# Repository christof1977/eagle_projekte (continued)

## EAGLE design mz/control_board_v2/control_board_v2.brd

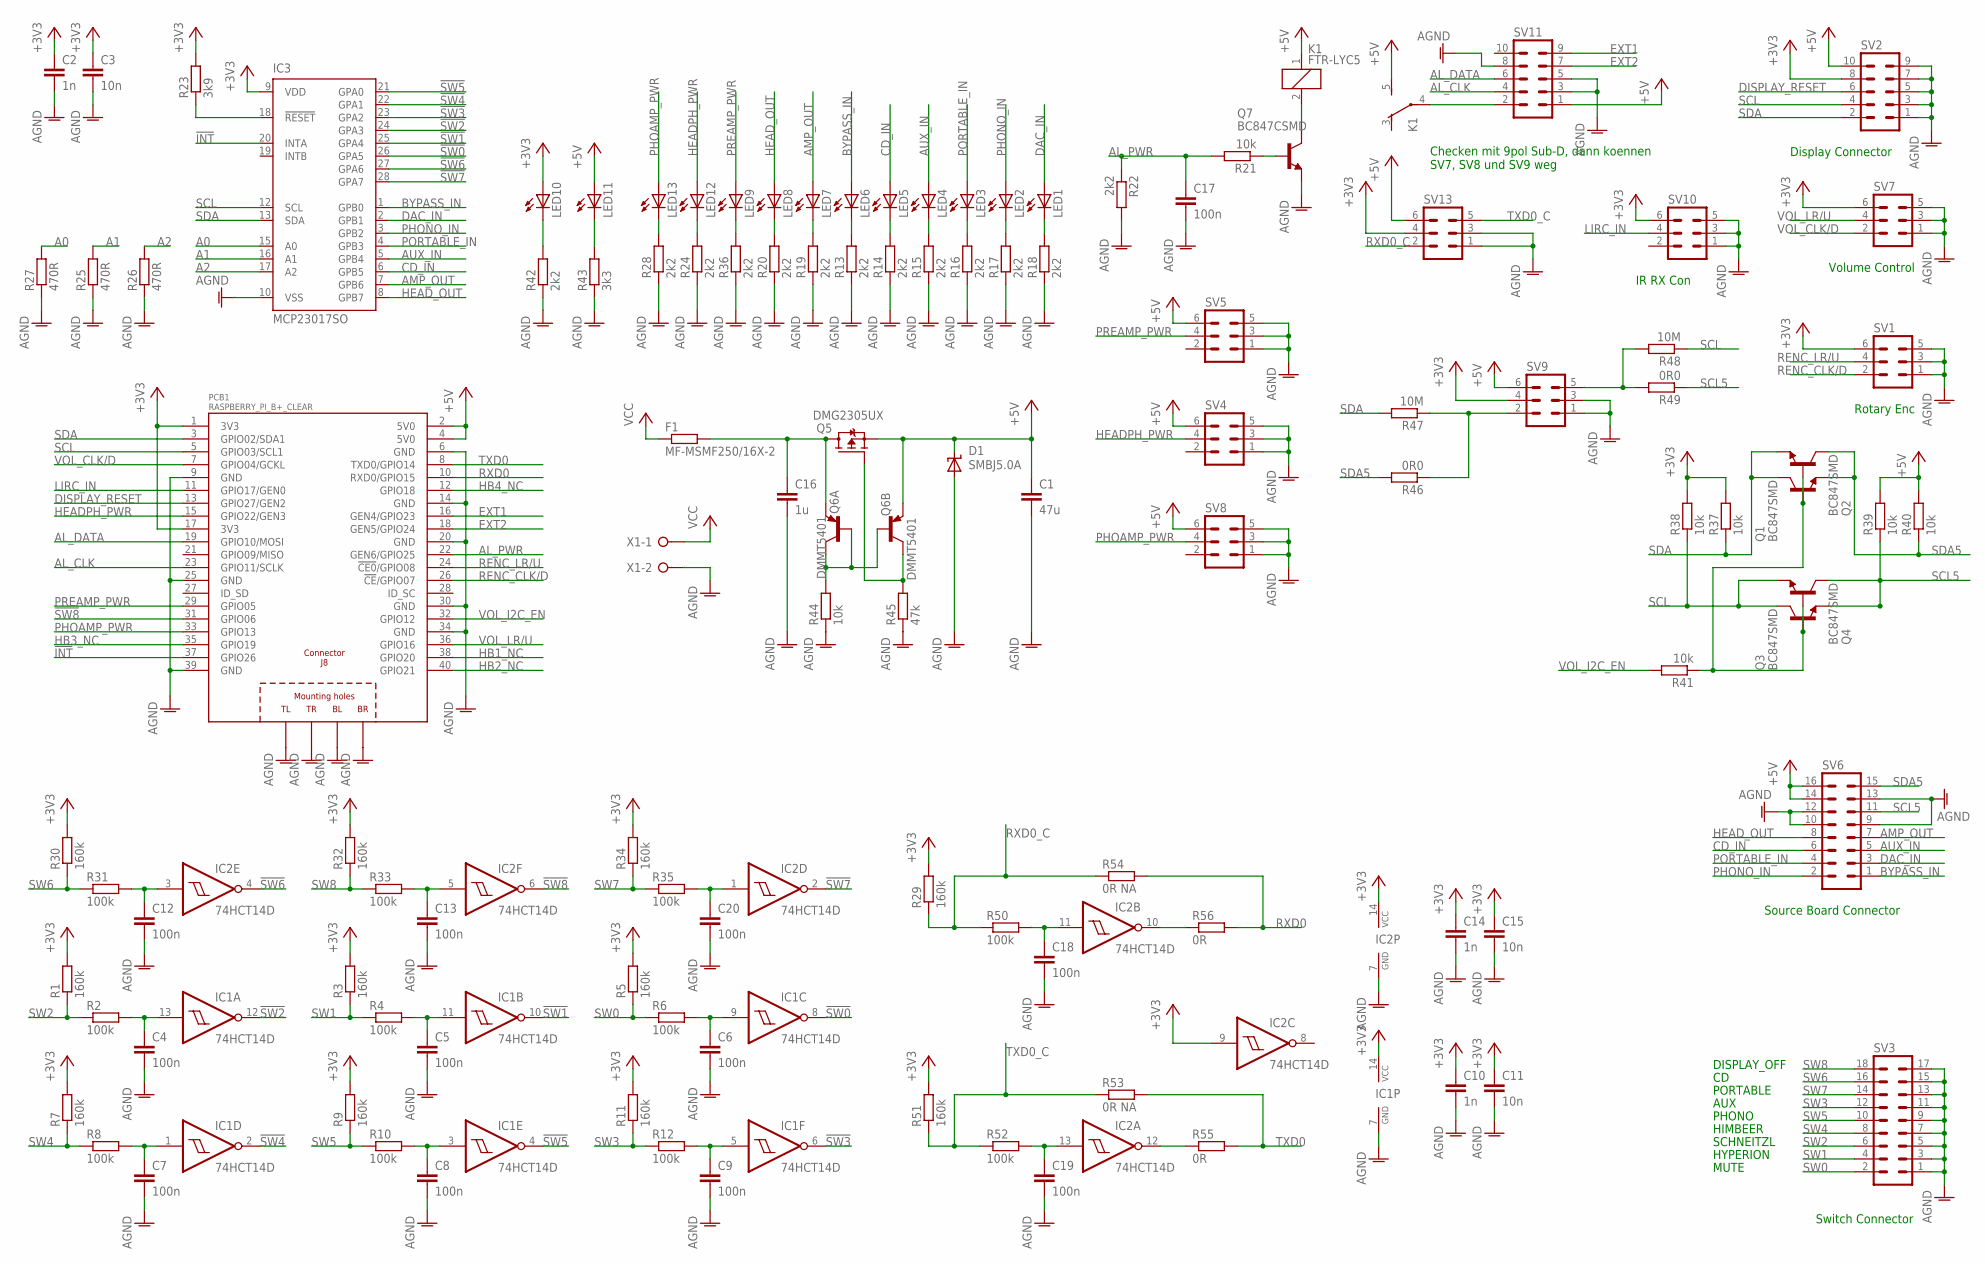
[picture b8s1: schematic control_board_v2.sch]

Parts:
C1: 47u; C1812
C2, C10, C14: 1n; C0603
C3, C11, C15: 10n; C0603
C4, C5, C6, C7, C8, C9, C12, C13, C17, C18, C19, C20: 100n; C0603
C16: 1u; C1206
D1: SMBJ5.0A; SMBJ
F1: MF-MSMF250/16X-2; 1812X7R
IC1, IC2: 74HCT14D; SO14
IC3: MCP23017SO; SO28W
K1: FTR-LYC5; FTR-LYC
LED1, LED2, LED3, LED4, LED5, LED6, LED7, LED8, LED9, LED10, LED11, LED12, LED13: LEDCHIPLED_0603; CHIPLED_0603
PCB1: RASPBERRY_PI_B+_CLEAR; RASPBERRY_PI_PLUS_CLEAR
Q1, Q2, Q3, Q4: BC847SMD; SOT23
Q5: DMG2305UX; SOT23
Q6: DMMT5401; SOT23-6
Q7: BC847CSMD; SOT23
R1, R3, R5, R7, R9, R11, R29, R30, R32, R34, R51: 160k; R0603
R2, R4, R6, R8, R10, R12, R31, R33, R35, R50, R52: 100k; R0603
R13, R14, R15, R16, R17, R18, R19, R20, R22, R24, R28, R36, R42: 2k2; R0603
R21, R38, R39, R40, R44: 10k; R0603
R23: 3k9; R1206
R25, R26, R27: 470R; R0603
R37, R41: 10k; R1206
R43: 3k3; R0603
R45: 47k; R0603
R46, R49: 0R0; R0603
R47, R48: 10M; R0603
R53, R54: 0R NA; R0603
R55, R56: 0R; R0603
SV1, SV4, SV5, SV7, SV8, SV9, SV10, SV13: MA03-2B; MA03-2_BORDER
SV2, SV11: MA05-2B; MA05-2_BORDER
SV3: MA09-2B; MA09-2_BORDER
SV6: MA08-2B; MA08-2_BORDER
X1: W237-02P; W237-132

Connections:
!INT: IC3.20 (INTA), PCB1.37 (GPIO26)
!SW0: IC1.8 (O), IC3.26 (GPA5)
!SW1: IC1.10 (O), IC3.25 (GPA4)
!SW2: IC1.12 (O), IC3.24 (GPA3)
!SW3: IC1.6 (O), IC3.23 (GPA2)
!SW4: IC1.2 (O), IC3.22 (GPA1)
!SW5: IC1.4 (O), IC3.21 (GPA0)
!SW6: IC2.4 (O), IC3.27 (GPA6)
!SW7: IC2.2 (O), IC3.28 (GPA7)
!SW8: IC2.6 (O), PCB1.31 (GPIO06)
+3V3: C2.1, C3.1, C10.1, C11.1, C14.1, C15.1, IC1.14 (VCC), IC2.9 (I), IC2.14 (VCC), IC3.9 (VDD), LED10.A, PCB1.1 (3V3), PCB1.17 (3V3), R1.2, R3.2, R5.2, R7.2, R9.2, R11.2, R23.2, R29.2, R30.2, R32.2, R34.2, R37.2, R38.2, R51.2, SV1.6, SV2.8, SV7.6, SV9.4, SV10.6, SV13.4
+5V: C1.1, D1.C, K1.1, K1.5 (S), LED11.A, PCB1.2 (5V0), PCB1.4 (5V0), Q5.2 (S), Q6.5 (E), R39.2, R40.2, SV2.10, SV4.6, SV5.6, SV6.14, SV6.16, SV8.6, SV9.6, SV11.1, SV13.6
A0: IC3.15 (A0), R27.2
A1: IC3.16 (A1), R25.2
A2: IC3.17 (A2), R26.2
AGND: C1.2, C2.2, C3.2, C4.2, C5.2, C6.2, C7.2, C8.2, C9.2, C10.2, C11.2, C12.2, C13.2, C14.2, C15.2, C16.2, C17.2, C18.2, C19.2, C20.2, D1.A, IC1.7 (GND), IC2.7 (GND), IC3.10 (VSS), PCB1.6 (GND), PCB1.9 (GND), PCB1.14 (GND), PCB1.20 (GND), PCB1.25 (GND), PCB1.30 (GND), PCB1.34 (GND), PCB1.39 (GND), PCB1.PE_BL (BL), PCB1.PE_BR (BR), PCB1.PE_TL (TL), PCB1.PE_TR (TR), Q7.2 (E), R13.1, R14.1, R15.1, R16.1, R17.1, R18.1, R19.1, R20.1, R22.2, R24.1, R25.1, R26.1, R27.1, R28.1, R36.1, R42.1, R43.1, R44.1, R45.1, SV1.1, SV1.3, SV1.5, SV2.1, SV2.3, SV2.5, SV2.7, SV2.9, SV3.1, SV3.3, SV3.5, SV3.7, SV3.9, SV3.11, SV3.13, SV3.15, SV3.17, SV4.1, SV4.3, SV4.5, SV5.1, SV5.3, SV5.5, SV6.9, SV6.10, SV6.12, SV6.13, SV7.1, SV7.3, SV7.5, SV8.1, SV8.3, SV8.5, SV9.1, SV9.3, SV10.1, SV10.3, SV10.5, SV11.3, SV11.5, SV11.8, SV13.1, SV13.3, X1.2
AL_CLK: PCB1.23 (GPIO11/SCLK), SV11.4
AL_DATA: PCB1.19 (GPIO10/MOSI), SV11.6
AL_PWR: C17.1, PCB1.22 (GEN6/GPIO25), R21.2, R22.1
AMP_OUT: IC3.7 (GPB6), LED7.A, SV6.7
AUX_IN: IC3.5 (GPB4), LED4.A, SV6.5
BYPASS_IN: IC3.1 (GPB0), LED6.A, SV6.1
CD_IN: IC3.6 (GPB5), LED5.A, SV6.6
DAC_IN: IC3.2 (GPB1), LED1.A, SV6.3
DISPLAY_RESET: PCB1.13 (GPIO27/GEN2), SV2.6
EXT1: PCB1.16 (GEN4/GPIO23), SV11.9
EXT2: PCB1.18 (GEN5/GPIO24), SV11.7
HB1_NC: PCB1.38 (GPIO20)
HB2_NC: PCB1.40 (GPIO21)
HB3_NC: PCB1.35 (GPIO19)
HB4_NC: PCB1.12 (GPIO18)
HEADPH_PWR: LED12.A, PCB1.15 (GPIO22/GEN3), SV4.4
HEAD_OUT: IC3.8 (GPB7), LED8.A, SV6.8
LIRC_IN: PCB1.11 (GPIO17/GEN0), SV10.4
unnamed: C20.1, IC2.1 (I), R35.2
unnamed: LED13.C, R28.2
unnamed: LED12.C, R24.2
unnamed: LED9.C, R36.2
unnamed: LED8.C, R20.2
unnamed: LED7.C, R19.2
unnamed: LED6.C, R13.2
unnamed: LED3.C, R16.2
unnamed: LED4.C, R15.2
unnamed: LED5.C, R14.2
unnamed: C12.1, IC2.3 (I), R31.2
unnamed: C4.1, IC1.13 (I), R2.2
unnamed: C13.1, IC2.5 (I), R33.2
unnamed: C5.1, IC1.11 (I), R4.2
unnamed: IC3.18 (!RESET), R23.1
unnamed: C6.1, IC1.9 (I), R6.2
unnamed: Q1.1 (B), Q2.1 (B), Q3.1 (B), Q4.1 (B), R41.1
unnamed: C7.1, IC1.1 (I), R8.2
unnamed: Q6.1 (C), Q6.2 (B), Q6.3 (B), R44.2
unnamed: C8.1, IC1.3 (I), R10.2
unnamed: K1.4, SV11.2
unnamed: LED11.C, R43.2
unnamed: C9.1, IC1.5 (I), R12.2
unnamed: LED10.C, R42.2
unnamed: Q5.1 (G), Q6.4 (C), R45.2
unnamed: C16.1, F1.2, Q5.3 (D), Q6.6 (E)
unnamed: Q7.1 (B), R21.1
unnamed: K1.2, Q7.3 (C)
unnamed: C18.1, IC2.11 (I), R50.2
unnamed: LED1.C, R18.2
unnamed: C19.1, IC2.13 (I), R52.2
unnamed: IC2.12 (O), R55.1
unnamed: IC2.10 (O), R56.1
unnamed: LED2.C, R17.2
unnamed: R48.2, R49.2, SV9.5
unnamed: R46.1, R47.1, SV9.2
PHOAMP_PWR: LED13.A, PCB1.33 (GPIO13), SV8.4
PHONO_IN: IC3.3 (GPB2), LED2.A, SV6.2
PORTABLE_IN: IC3.4 (GPB3), LED3.A, SV6.4
PREAMP_PWR: LED9.A, PCB1.29 (GPIO05), SV5.4
RENC_CLK/D: PCB1.26 (!CE!/GPIO07), SV1.2
RENC_LR/U: PCB1.24 (!CE0!/GPIO08), SV1.4
RXD0: PCB1.10 (RXD0/GPIO15), R54.2, R56.2
RXD0_C: R29.1, R50.1, R54.1, SV13.2
SCL: IC3.12 (SCL), PCB1.5 (GPIO03/SCL1), Q3.3 (C), Q4.2 (E), R38.1, R48.1, SV2.4
SCL5: Q3.2 (E), Q4.3 (C), R39.1, R49.1, SV6.11
SDA: IC3.13 (SDA), PCB1.3 (GPIO02/SDA1), Q1.3 (C), Q2.2 (E), R37.1, R47.2, SV2.2
SDA5: Q1.2 (E), Q2.3 (C), R40.1, R46.2, SV6.15
SW0: R5.1, R6.1, SV3.2
SW1: R3.1, R4.1, SV3.4
SW2: R1.1, R2.1, SV3.6
SW3: R11.1, R12.1, SV3.12
SW4: R7.1, R8.1, SV3.8
SW5: R9.1, R10.1, SV3.10
SW6: R30.1, R31.1, SV3.16
SW7: R34.1, R35.1, SV3.14
SW8: R32.1, R33.1, SV3.18
TXD0: PCB1.8 (TXD0/GPIO14), R53.2, R55.2
TXD0_C: R51.1, R52.1, R53.1, SV13.5
VCC: F1.1, X1.1
VOL_CLK/D: PCB1.7 (GPIO04/GCKL), SV7.2
VOL_I2C_EN: PCB1.32 (GPIO12), R41.2
VOL_LR/U: PCB1.36 (GPIO16), SV7.4

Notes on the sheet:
Display Connector
Source Board Connector
Switch Connector
Volume Control
IR RX Con
Checken mit 9pol Sub-D, dann koennen SV7, SV8 und SV9 weg
PORTABLE
AUX
PHONO
HIMBEER
SCHNEITZL
HYPERION
MUTE
DISPLAY_OFF
Rotary Enc

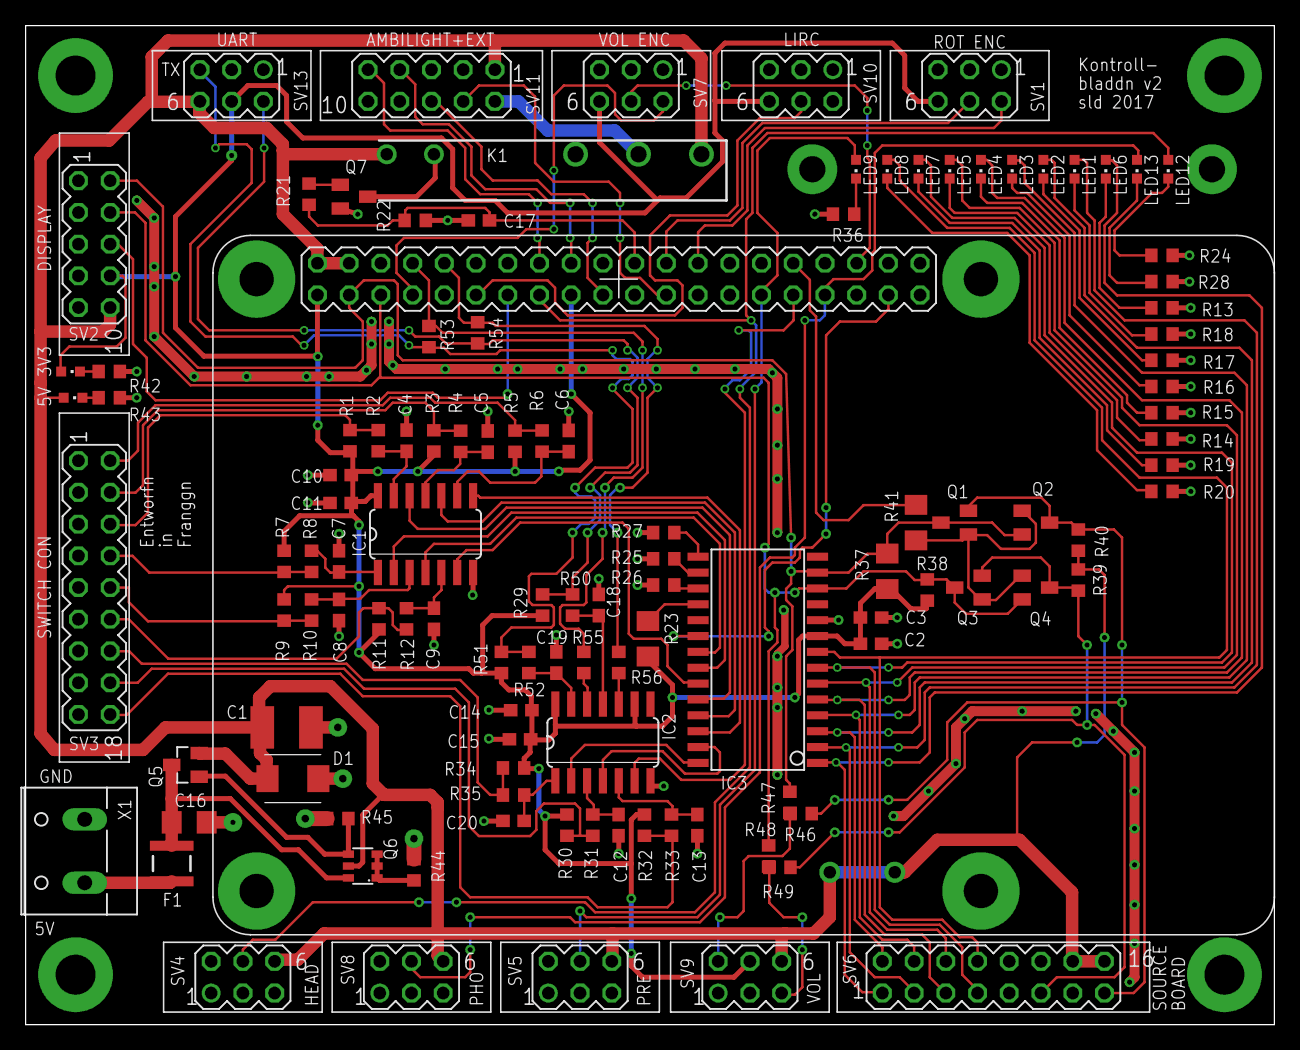
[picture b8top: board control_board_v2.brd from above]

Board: 2 copper layers, 100.0 x 80.0 mm, 116 parts (0 on the bottom side), 93 nets.

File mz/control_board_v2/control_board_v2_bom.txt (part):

Stückliste exportiert aus /Volumes/christof's home/eagle/mz/control_board_v2/control_board_v2.sch am 21.12.17 20:57

Qty Value                 Device                Package                 Parts                                                                            Description                                                MF        MPN           OC_FARNELL OC_NEWARK
13                        LEDCHIPLED_0603       CHIPLED_0603            LED1, LED2, LED3, LED4, LED5, LED6, LED7, LED8, LED9, LED10, LED11, LED12, LED13 LED                                                                                                    
8                         MA03-2B               MA03-2_BORDER           SV1, SV4, SV5, SV7, SV8, SV9, SV10, SV13                                         PIN HEADER                                                                                             
2                         MA05-2B               MA05-2_BORDER           SV2, SV11                                                                        PIN HEADER                                                                                             
1                         MA08-2B               MA08-2_BORDER           SV6                                                                              PIN HEADER                                                                                             
1                         MA09-2B               MA09-2_BORDER           SV3                                                                              PIN HEADER                                                                                             
1                         W237-02P              W237-132                X1                                                                               WAGO SREW CLAMP                                                                    unknown    unknown  
2   0R                    R-EU_R0603            R0603                   R55, R56                                                                         RESISTOR, European symbol                                                                              
2   0R NA                 R-EU_R0603            R0603                   R53, R54                                                                         RESISTOR, European symbol                                                                              
2   0R0                   R-EU_R0603            R0603                   R46, R49                                                                         RESISTOR, European symbol                                                                              
11  100k                  R-EU_R0603            R0603                   R2, R4, R6, R8, R10, R12, R31, R33, R35, R50, R52                                RESISTOR, European symbol                                                                              
12  100n                  C-EUC0603             C0603                   C4, C5, C6, C7, C8, C9, C12, C13, C17, C18, C19, C20                             CAPACITOR, European symbol                                                                             
2   10M                   R-EU_R0603            R0603                   R47, R48                                                                         RESISTOR, European symbol                                                                              
5   10k                   R-EU_R0603            R0603                   R21, R38, R39, R40, R44                                                          RESISTOR, European symbol                                                                              
2   10k                   R-EU_R1206            R1206                   R37, R41                                                                         RESISTOR, European symbol                                                                              
3   10n                   C-EUC0603             C0603                   C3, C11, C15                                                                     CAPACITOR, European symbol                                                                             
11  160k                  R-EU_R0603            R0603                   R1, R3, R5, R7, R9, R11, R29, R30, R32, R34, R51                                 RESISTOR, European symbol                                                                              
3   1n                    C-EUC0603             C0603                   C2, C10, C14                                                                     CAPACITOR, European symbol                                                                             
1   1u                    C-EUC1206             C1206                   C16                                                                              CAPACITOR, European symbol                                                                             
13  2k2                   R-EU_R0603            R0603                   R13, R14, R15, R16, R17, R18, R19, R20, R22, R24, R28, R36, R42                  RESISTOR, European symbol                                                                              
1   3k3                   R-EU_R0603            R0603                   R43                                                                              RESISTOR, European symbol                                                                              
1   3k9                   R-EU_R1206            R1206                   R23                                                                              RESISTOR, European symbol                                                                              
3   470R                  R-EU_R0603            R0603                   R25, R26, R27                                                                    RESISTOR, European symbol                                                                              
1   47k                   R-EU_R0603            R0603                   R45                                                                              RESISTOR, European symbol                                                                              
1   47u                   C-EUC1812             C1812                   C1                                                                               CAPACITOR, European symbol                                                                             
2   74HCT14D              74HCT14D              SO14                    IC1, IC2                                                                         Hex schmitt trigger INVERTER                                                                           
1   BC847CSMD             BC847CSMD             SOT23                   Q7                                                                               NPN Transistor                                                                                         
4   BC847SMD              BC847SMD              SOT23                   Q1, Q2, Q3, Q4                                                                   NPN Transistor                                                                                         
1   DMG2305UX             DMG2305UX             SOT23                   Q5                                                                                                                                                                                      
1   DMMT5401              DMMT5401              SOT23-6                 Q6                                                                                                                                                                                      
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
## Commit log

2017-11-29 Added project esp_thermometer
2018-11-25 Fertiger Schaltplan und Layout esp-thermometer
2018-12-01 Alte Eagle-Libs eingecheckt
2018-12-01 Ampi v2 eingecheckt
2018-12-01 Ampi v1 eingecheckt
2018-12-01 Alten PIC-Webserver eingecheeckt
2018-12-01 gitignore rein, DS_Store raus
